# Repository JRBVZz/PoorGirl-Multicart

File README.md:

### POORGIRL - дешевый картридж-многоигровка для Famicom/Dendy

Данный проект является компиляцией [COOLGIRL](https://github.com/ClusterM/coolgirl-famicom-multicart) **Алексея Clustera** и китайских флэшкартриджей. Допускается установка **EPM570T100** или **EPM240T100**, но учтите, что в EPM240 влезет небольшое количество мапперов из-за малого объема логических ячеек. Картридж поддерживает сохранение только одной игры, если вы запустите другую игру с поддержкой сохранений, то записи от предыдущей игры пропадут.  
  
Характеристики:  
* PRG ROM: max 128 MiB
* CHR RAM: max 256 KiB
* PRG RAM: 32 KiB, FRAM или SRAM с батарейкой

Проект создан в [**KiCad 9**](https://www.kicad.org/).

### Сборка

#### BoM и Schematic
[BoM](PoorGirl-Docs/PoorGirl1.1-BOM.jpg)  
  
[Schematic](PoorGirl-Docs/PoorGirl1.1-Schematic.pdf)

Элементы **R1, D1, C8** нужны только для software reset, по умолчанию в прошивке он отключен.  
Элементы **BT1, D2, D3, R6** нужны для питания SRAM, если предполагается установка FRAM, то достаточно запаять перемычку **"FRAM"**.  
Если вы используете EPM570T100, то замкните две перемычки **"EPM570 ONLY"** на обратной стороне платы.

#### PCB

* Layers: 2
* PCB Thickness: 1.2mm
* Рекомендуется ENIG покрытие

#### Firmware
В архиве **PoorGirl-Firmware/PoorGirl-Firmware.zip** находятся проекты для Quartus. Все мапперы не влезут в EPM570T100 (тем более в EPM240T100), поэтому выберите нужные в начале файла с verilog кодом **Cool2Poor.v**, чтобы они поместились в 570 (240) логических ячеек.  
По умолчанию reset отключен, поэтому при сбросе приставки появится начальный экран текущей игры, а не меню. Для **включения reset** измените значение `parameter RESET_COMBINATION = 8'b0` на `8'b11010010`, но учтите, что reset занимает около 80 логических ячеек.  
Оптимизированные прошивки можно найти на [форуме Emu-Land.net](https://www.emu-land.net/forum/index.php/topic,82545.0.html), но нужно будет изменить назначения выводов в **Quartus Pin Planner**.

#### Сборка ROM
Для сборки многоигровки с меню можно использовать [COOLGIRL Multirom Builder](https://github.com/ClusterM/coolgirl-multirom-builder). Чтобы работали сохранения, замените файл **saves.asm** на [PoorGirl-Docs/saves.asm](PoorGirl-Docs/saves.asm). Для записи можно использовать [Famicom/NES Dumper/Writer](https://github.com/ClusterM/famicom-dumper-writer), или программатор.

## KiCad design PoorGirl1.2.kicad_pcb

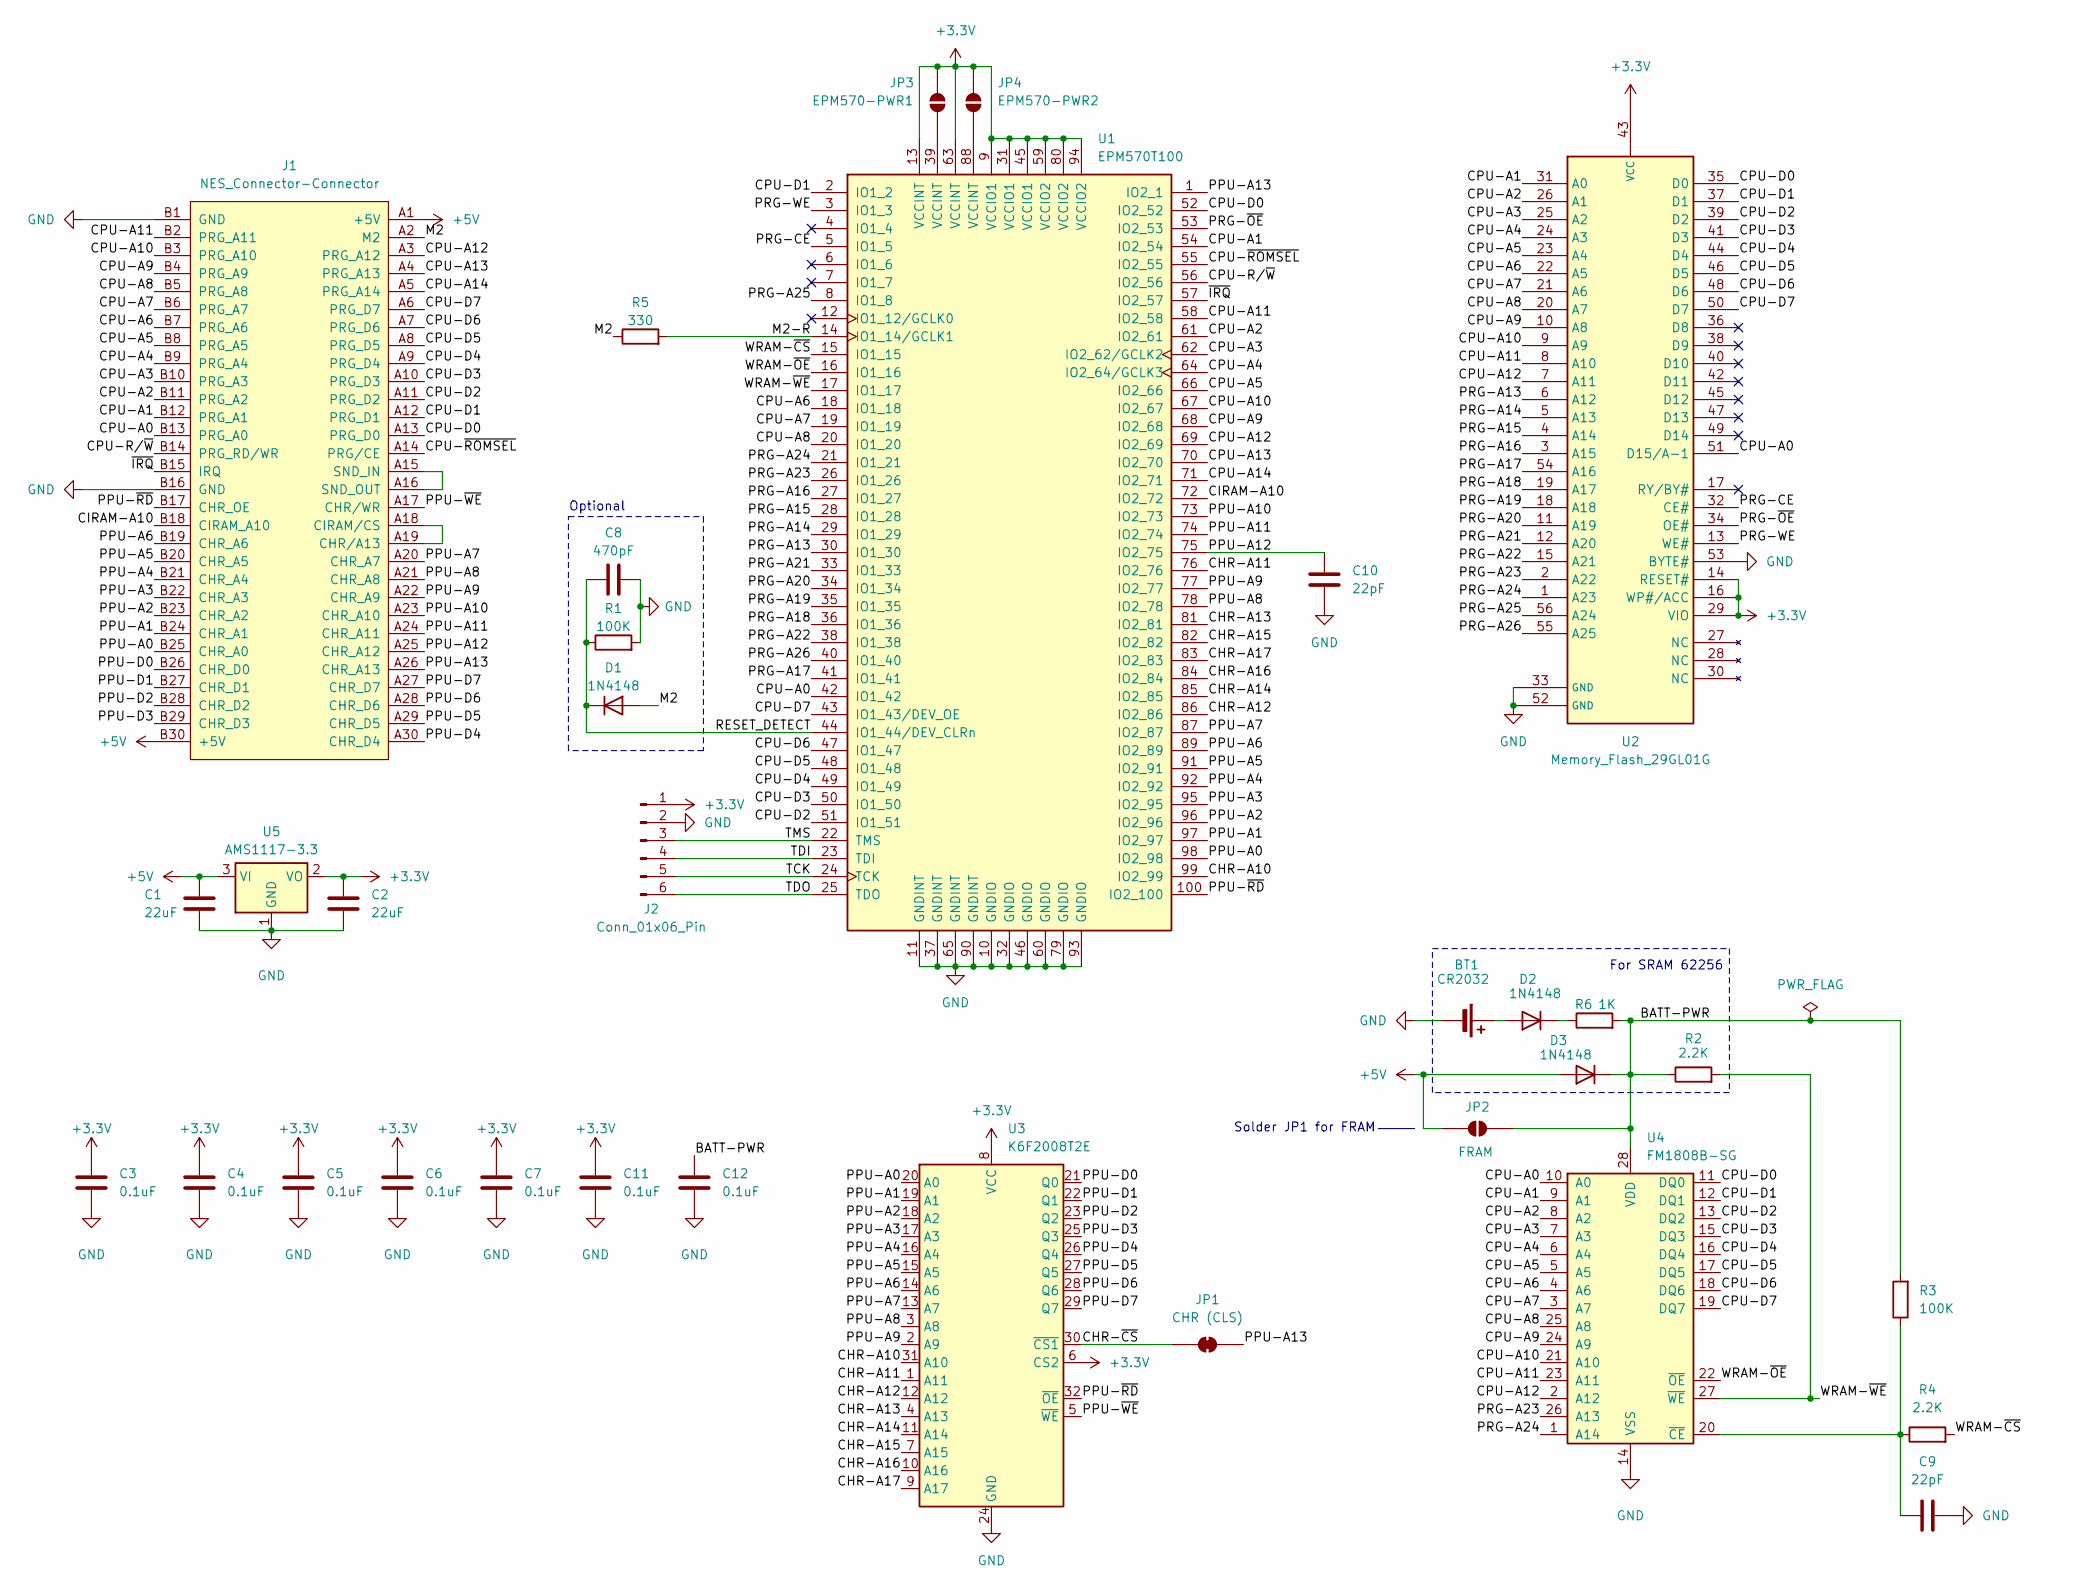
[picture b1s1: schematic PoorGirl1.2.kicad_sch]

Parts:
BT1: CR2032; BatteryHolder_Keystone_1060_1x2032
C1, C2: 22uF; C_0805_2012Metric
C3, C4, C5, C6, C7, C11, C12: 0.1uF; C_0603_1608Metric_Pad1.08x0.95mm_HandSolder
C8: 470pF; C_0805_2012Metric
C9, C10: 22pF; C_0805_2012Metric
D1, D2, D3: 1N4148; D_SOD-123
J1: NES_Connector-Connector; NES_Connector_L
J2: Conn_01x06_Pin; PinHeader_1x06_P2.54mm_Vertical
JP1: CHR (CLS); SolderJumper-2_P1.3mm_Bridged_RoundedPad1.0x1.5mm
JP2: FRAM; SolderJumper-2_P1.3mm_Open_RoundedPad1.0x1.5mm
JP3: EPM570-PWR1; SolderJumper-2_P1.3mm_Open_RoundedPad1.0x1.5mm
JP4: EPM570-PWR2; SolderJumper-2_P1.3mm_Open_RoundedPad1.0x1.5mm
R1, R3: 100K; R_0805_2012Metric
R2, R4: 2.2K; R_0805_2012Metric
R5: 330; R_0805_2012Metric
R6: 1K; R_0805_2012Metric
U1: EPM570T100; LQFP-100_14x14mm_P0.5mm
U2: Memory_Flash_29GL01G; TSOP-I-56_18.4x14mm_P0.5mm
U3: K6F2008T2E; TSOP-I-32_11.8x8mm_P0.5mm
U4: FM1808B-SG; SOP-28
U5: AMS1117-3.3; SOT-223-3_TabPin2

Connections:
+3.3V: C2.1, C3.1, C4.1, C5.1, C6.1, C7.1, C11.1, J2.1, JP3.2 (B), JP4.2 (B), U1.9 (VCCIO1), U1.13 (VCCINT), U1.31 (VCCIO1), U1.45 (VCCIO1), U1.59 (VCCIO2), U1.63 (VCCINT), U1.80 (VCCIO2), U1.94 (VCCIO2), U2.14 (RESET#), U2.16 (WP#/ACC), U2.29 (VIO), U2.43 (VCC), U3.6 (CS2), U3.8 (VCC), U5.2 (VO)
+5V: C1.1, D3.2 (A), J1.A1 (+5V), J1.B30 (+5V), JP2.1 (A), U5.3 (VI)
/BATT-PWR: C12.1, D3.1 (K), JP2.2 (B), R2.1, R3.2, R6.2, U4.28 (VDD)
/CHR-A10: U1.99 (IO2_99), U3.31 (A10)
/CHR-A11: U1.76 (IO2_76), U3.1 (A11)
/CHR-A12: U1.86 (IO2_86), U3.12 (A12)
/CHR-A13: U1.81 (IO2_81), U3.4 (A13)
/CHR-A14: U1.85 (IO2_85), U3.11 (A14)
/CHR-A15: U1.82 (IO2_82), U3.7 (A15)
/CHR-A16: U1.84 (IO2_84), U3.10 (A16)
/CHR-A17: U1.83 (IO2_83), U3.9 (A17)
/CHR-~CS: JP1.1 (A), U3.30 (~CS1)
/CIRAM-A10: J1.B18 (CIRAM_A10), U1.72 (IO2_72)
/CPU-A0: J1.B13 (PRG_A0), U1.42 (IO1_42), U2.51 (D15/A-1), U4.10 (A0)
/CPU-A1: J1.B12 (PRG_A1), U1.54 (IO2_54), U2.31 (A0), U4.9 (A1)
/CPU-A2: J1.B11 (PRG_A2), U1.61 (IO2_61), U2.26 (A1), U4.8 (A2)
/CPU-A3: J1.B10 (PRG_A3), U1.62 (IO2_62/GCLK2), U2.25 (A2), U4.7 (A3)
/CPU-A4: J1.B9 (PRG_A4), U1.64 (IO2_64/GCLK3), U2.24 (A3), U4.6 (A4)
/CPU-A5: J1.B8 (PRG_A5), U1.66 (IO2_66), U2.23 (A4), U4.5 (A5)
/CPU-A6: J1.B7 (PRG_A6), U1.18 (IO1_18), U2.22 (A5), U4.4 (A6)
/CPU-A7: J1.B6 (PRG_A7), U1.19 (IO1_19), U2.21 (A6), U4.3 (A7)
/CPU-A8: J1.B5 (PRG_A8), U1.20 (IO1_20), U2.20 (A7), U4.25 (A8)
/CPU-A9: J1.B4 (PRG_A9), U1.68 (IO2_68), U2.10 (A8), U4.24 (A9)
/CPU-A10: J1.B3 (PRG_A10), U1.67 (IO2_67), U2.9 (A9), U4.21 (A10)
/CPU-A11: J1.B2 (PRG_A11), U1.58 (IO2_58), U2.8 (A10), U4.23 (A11)
/CPU-A12: J1.A3 (PRG_A12), U1.69 (IO2_69), U2.7 (A11), U4.2 (A12)
/CPU-A13: J1.A4 (PRG_A13), U1.70 (IO2_70)
/CPU-A14: J1.A5 (PRG_A14), U1.71 (IO2_71)
/CPU-D0: J1.A13 (PRG_D0), U1.52 (IO2_52), U2.35 (D0), U4.11 (DQ0)
/CPU-D1: J1.A12 (PRG_D1), U1.2 (IO1_2), U2.37 (D1), U4.12 (DQ1)
/CPU-D2: J1.A11 (PRG_D2), U1.51 (IO1_51), U2.39 (D2), U4.13 (DQ2)
/CPU-D3: J1.A10 (PRG_D3), U1.50 (IO1_50), U2.41 (D3), U4.15 (DQ3)
/CPU-D4: J1.A9 (PRG_D4), U1.49 (IO1_49), U2.44 (D4), U4.16 (DQ4)
/CPU-D5: J1.A8 (PRG_D5), U1.48 (IO1_48), U2.46 (D5), U4.17 (DQ5)
/CPU-D6: J1.A7 (PRG_D6), U1.47 (IO1_47), U2.48 (D6), U4.18 (DQ6)
/CPU-D7: J1.A6 (PRG_D7), U1.43 (IO1_43/DEV_OE), U2.50 (D7), U4.19 (DQ7)
/CPU-R/~W: J1.B14 (PRG_RD/WR), U1.56 (IO2_56)
/CPU-~ROMSEL: J1.A14 (PRG/CE), U1.55 (IO2_55)
/M2: D1.2 (A), J1.A2 (M2), R5.1
/M2-R: R5.2, U1.14 (IO1_14/GCLK1)
/PPU-A0: J1.B25 (CHR_A0), U1.98 (IO2_98), U3.20 (A0)
/PPU-A1: J1.B24 (CHR_A1), U1.97 (IO2_97), U3.19 (A1)
/PPU-A2: J1.B23 (CHR_A2), U1.96 (IO2_96), U3.18 (A2)
/PPU-A3: J1.B22 (CHR_A3), U1.95 (IO2_95), U3.17 (A3)
/PPU-A4: J1.B21 (CHR_A4), U1.92 (IO2_92), U3.16 (A4)
/PPU-A5: J1.B20 (CHR_A5), U1.91 (IO2_91), U3.15 (A5)
/PPU-A6: J1.B19 (CHR_A6), U1.89 (IO2_89), U3.14 (A6)
/PPU-A7: J1.A20 (CHR_A7), U1.87 (IO2_87), U3.13 (A7)
/PPU-A8: J1.A21 (CHR_A8), U1.78 (IO2_78), U3.3 (A8)
/PPU-A9: J1.A22 (CHR_A9), U1.77 (IO2_77), U3.2 (A9)
/PPU-A10: J1.A23 (CHR_A10), U1.73 (IO2_73)
/PPU-A11: J1.A24 (CHR_A11), U1.74 (IO2_74)
/PPU-A12: C10.2, J1.A25 (CHR_A12), U1.75 (IO2_75)
/PPU-A13: J1.A26 (CHR_A13), JP1.2 (B), U1.1 (IO2_1)
/PPU-D0: J1.B26 (CHR_D0), U3.21 (Q0)
/PPU-D1: J1.B27 (CHR_D1), U3.22 (Q1)
/PPU-D2: J1.B28 (CHR_D2), U3.23 (Q2)
/PPU-D3: J1.B29 (CHR_D3), U3.25 (Q3)
/PPU-D4: J1.A30 (CHR_D4), U3.26 (Q4)
/PPU-D5: J1.A29 (CHR_D5), U3.27 (Q5)
/PPU-D6: J1.A28 (CHR_D6), U3.28 (Q6)
/PPU-D7: J1.A27 (CHR_D7), U3.29 (Q7)
/PPU-~RD: J1.B17 (CHR_OE), U1.100 (IO2_100), U3.32 (~OE)
/PPU-~WE: J1.A17 (CHR/WR), U3.5 (~WE)
/PRG-A13: U1.30 (IO1_30), U2.6 (A12)
/PRG-A14: U1.29 (IO1_29), U2.5 (A13)
/PRG-A15: U1.28 (IO1_28), U2.4 (A14)
/PRG-A16: U1.27 (IO1_27), U2.3 (A15)
/PRG-A17: U1.41 (IO1_41), U2.54 (A16)
/PRG-A18: U1.36 (IO1_36), U2.19 (A17)
/PRG-A19: U1.35 (IO1_35), U2.18 (A18)
/PRG-A20: U1.34 (IO1_34), U2.11 (A19)
/PRG-A21: U1.33 (IO1_33), U2.12 (A20)
/PRG-A22: U1.38 (IO1_38), U2.15 (A21)
/PRG-A23: U1.26 (IO1_26), U2.2 (A22), U4.26 (A13)
/PRG-A24: U1.21 (IO1_21), U2.1 (A23), U4.1 (A14)
/PRG-A25: U1.8 (IO1_8), U2.56 (A24)
/PRG-A26: U1.40 (IO1_40), U2.55 (A25)
/PRG-CE: U1.5 (IO1_5), U2.32 (CE#)
/PRG-WE: U1.3 (IO1_3), U2.13 (WE#)
/PRG-~OE: U1.53 (IO2_53), U2.34 (OE#)
/RESET_DETECT: C8.1, D1.1 (K), R1.1, U1.44 (IO1_44/DEV_CLRn)
/TCK: J2.5, U1.24 (TCK)
/TDI: J2.4, U1.23 (TDI)
/TDO: J2.6, U1.25 (TDO)
/TMS: J2.3, U1.22 (TMS)
/WRAM-~CS: R4.2, U1.15 (IO1_15)
/WRAM-~OE: U1.16 (IO1_16), U4.22 (~OE)
/WRAM-~WE: R2.2, U1.17 (IO1_17), U4.27 (~WE)
/~IRQ: J1.B15 (IRQ), U1.57 (IO2_57)
GND: BT1.2 (-), C1.2, C2.2, C3.2, C4.2, C5.2, C6.2, C7.2, C8.2, C9.2, C10.1, C11.2, C12.2, J1.B1 (GND), J1.B16 (GND), J2.2, R1.2, U1.10 (GNDIO), U1.11 (GNDINT), U1.32 (GNDIO), U1.37 (GNDINT), U1.46 (GNDIO), U1.60 (GNDIO), U1.65 (GNDINT), U1.79 (GNDIO), U1.90 (GNDINT), U1.93 (GNDIO), U2.33 (GND), U2.52 (GND), U2.53 (BYTE#), U3.24 (GND), U4.14 (VSS), U5.1 (GND)
unnamed: BT1.1 (+), D2.2 (A)
unnamed: D2.1 (K), R6.1
unnamed: J1.A18 (CIRAM/CS), J1.A19 (CHR/A13)
unnamed: J1.A15 (SND_IN), J1.A16 (SND_OUT)
unnamed: JP3.1 (A), U1.39 (VCCINT)
unnamed: JP4.1 (A), U1.88 (VCCINT)
unnamed: C9.1, R3.1, R4.1, U4.20 (~CE)

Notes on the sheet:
For SRAM 62256
Optional
Solder JP1 for FRAM

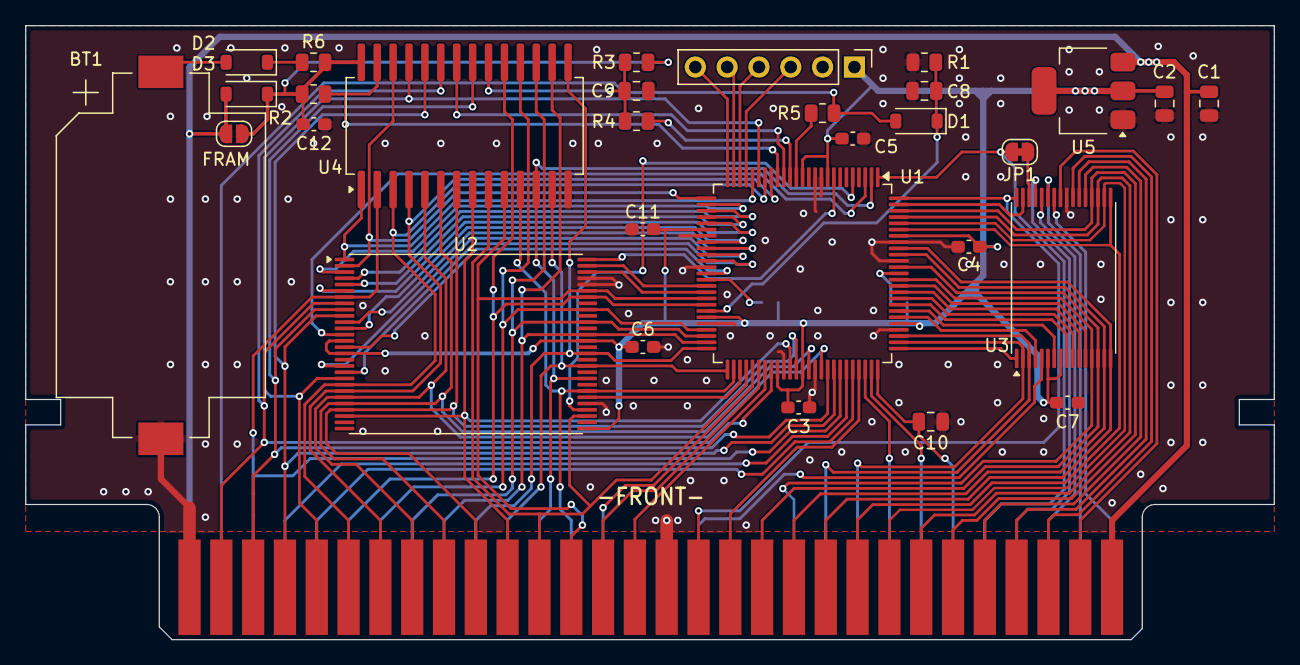
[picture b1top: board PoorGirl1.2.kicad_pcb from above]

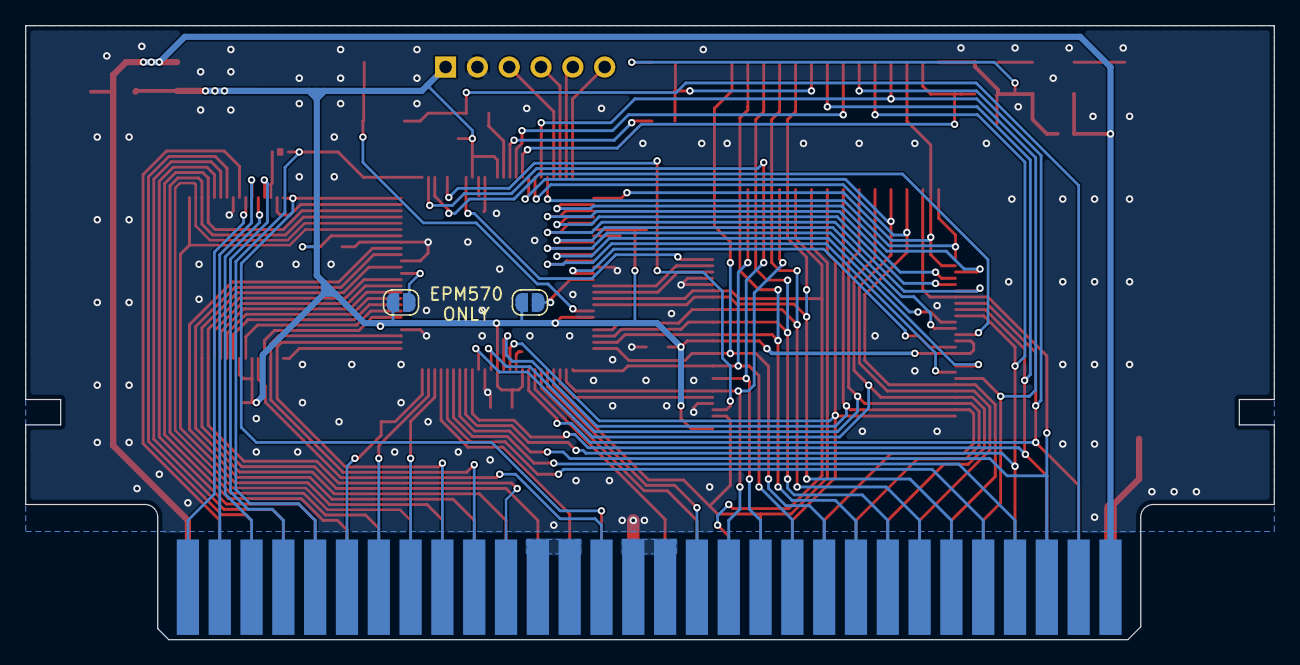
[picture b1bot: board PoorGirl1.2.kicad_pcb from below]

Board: 2 copper layers, 99.7 x 49.0 mm, 33 parts (2 on the bottom side), 98 nets.
